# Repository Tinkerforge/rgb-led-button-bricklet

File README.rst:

RGB LED Button Bricklet
=======================

This repository contains the firmware source code and the hardware design
files. The documentation generator configs can be found at
https://github.com/Tinkerforge/generators

Repository Content
------------------

software/:
 * examples/: Examples for all supported languages
 * build/: Compiled files
 * src/: Source code of firmware
 * Makefile: Makefile to build project

hardware/:
 * Contains KiCad project files and additionally schematics as PDF

datasheets/:
 * Contains datasheets for sensors and complex ICs that are used

Hardware
--------

The hardware is designed with the open source EDA Suite KiCad
(http://www.kicad.org). Before you are able to open the files,
you have to install the Tinkerforge kicad-libraries
(https://github.com/Tinkerforge/kicad-libraries). You can either clone
them directly in hardware/ or clone them in a separate folder and
symlink them into hardware/
(ln -s kicad_path/kicad-libraries project_path/hardware). After that you
can open the .pro file in hardware/ with KiCad and from there view and
modify the schematics and the PCB layout.

Software
--------

If you want to do your own Brick/Bricklet firmware development we highly
recommend that you use our build environment setup script and read the
tutorial (https://www.tinkerforge.com/en/doc/Tutorials/Tutorial_Build_Environment/Tutorial.html).

To compile the C code we recommend you to install the newest GNU Arm Embedded
Toolchain (https://launchpad.net/gcc-arm-embedded/+download).
You also need to install bricklib2 (https://github.com/Tinkerforge/bricklib2).

You can either clone it directly in software/src/ or clone it in a
separate folder and symlink it into software/src/
(ln -s bricklib_path/bricklib2 project_path/software/src/). Finally make sure to
have CMake installed (http://www.cmake.org/cmake/resources/software.html).

After that you can build the firmware by invoking make in software/.
The firmware (.zbin) can then be found in software/build/ and uploaded
with brickv (click button "Flashing" on start screen).

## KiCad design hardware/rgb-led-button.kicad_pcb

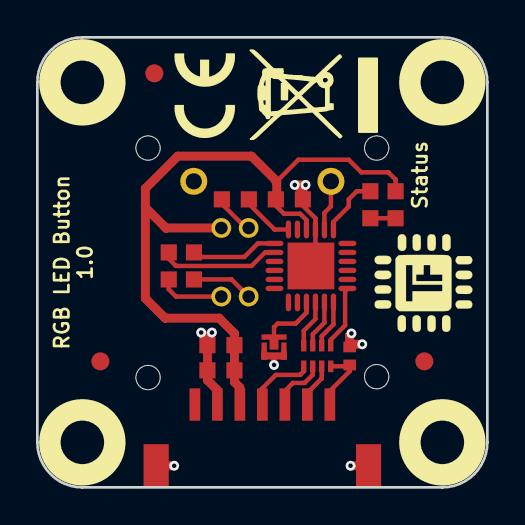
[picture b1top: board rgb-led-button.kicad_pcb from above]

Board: 2 copper layers, 25.0 x 25.0 mm, 22 parts (1 on the bottom side), 20 nets.

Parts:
C1: 220pF; C0402F
C2: 1uF; C0603F
C3: 10uF; C0603F
C4: 100nF; C0603F
D1: blue; D0603F
Fiducial_Mark: VAL**; Fiducial_Mark
Fiducial_Mark#2, Fiducial_Mark#3: VAL**; Fiducial_Mark
P1: CON-SENSOR; CON-SENSOR2
P2: Boot; SolderJumper
R1: 1k; R0603F
R2, R4: 15; R0603F
R3: 68; R0603F
RP1: 82; 4X0402
SW1: RGB_SWITCH_AD
U1: XMC1100-16; QFN24-4x4mm-0.5mm
U2, U3, U4, U5: DRILL; DRILL_NP
VAL: CE_5mm

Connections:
GND: C1.2, C2.1, C3.1, C4.1, P1.2, P1.EP, P2.1, SW1.2, U1.9, U1.EXP
unnamed: C1.1, P1.7, RP1.4
unnamed: D1.2, R1.2
unnamed: P1.4, RP1.1
unnamed: P1.5, RP1.2
unnamed: P1.6, RP1.3
unnamed: P2.2, U1.21
unnamed: R1.1, U1.7
unnamed: R2.2, SW1.B2
unnamed: R3.2, SW1.R2
unnamed: R4.2, SW1.G2
P1.0_HO: R4.1, U1.14
P1.1_HO: R3.1, U1.13
P1.2_HO: R2.1, U1.12
PinSwitch: SW1.1, U1.8
S-CLK: RP1.7, U1.23
S-CS: RP1.8, U1.22
S-MISO: RP1.5, U1.1
S-MOSI: RP1.6, U1.24
VCC: C2.2, C3.2, C4.2, D1.1, P1.3, SW1.C2, U1.10

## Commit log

2017-02-09 Add readme file
2017-02-09 initial check in
2017-02-14 Add schematic
2017-02-14 Add PCB
2017-02-14 Add fiducial marks and TF logo
2017-02-14 Add WEEE and CE logos
2017-03-01 Fix CE logo
2017-05-05 Change filtering to R/C circuit
2017-05-05 Add more 3d information (tbc)
2017-05-08 change button footprint, fix design
2017-05-08 add description
2017-05-22 add demo software for bricklet
    * primitive led dimming without pwm
2017-05-29 not finished: add led, reduce board size
2017-05-29 Fix name
2017-05-29 Add .gitignore
2017-05-29 Add Makefile and Changelog
2017-05-29 Add ccu dependency
2017-05-29 Use CCU4 to create PWM
2017-05-29 Remove define checking TODOs
2017-08-10 change bricklet to 25x25mm size
2017-08-10 fix text positions
2017-08-11 specify filter circuit
2017-08-14 fix rgb button footprint, specify resistors
2017-08-24 increase mounting holes
2017-08-24 fix button and status led pin
2017-08-24 Update gitignore file
2017-08-24 Use new ccu4_pwm function from hal
2017-08-24 Add rgb value calibration support
2017-08-24 Unify naming scheme
2017-09-08 add status led description text
2017-09-19 specify processor
2017-11-06 Add 3d information (final)
2017-11-06 Add 3d model (*.step & *.FCStd)
2017-11-06 Add final schematic
2017-11-09 Remove debugging
2017-11-16 rgb button status text fixed
2017-11-20 Rename schematic name
2017-11-20 Rename schematic properly
2017-11-20 add button datasheets
2017-11-20 Add calibration and bracket tests
2017-11-21 Remove WIP marker
2017-12-08 Add examples
2018-02-02 c: Fine-tune printf format
2018-02-19 javascript: Close div tag correctly
2018-02-20 Cleanup KiCad libraries config
    Ensure LibDir=kicad-libraries and LibName1=tinkerforge.
    Remove special library.
2018-03-05 Remove unused flash-size define
2018-05-11 Rename files
2018-05-24 perl: Use strict in examples
2018-05-28 example: Add missing dedicated print logic
2018-06-18 Change capacitor footprint(s) to C0402F
2018-06-28 Fix readme
2018-07-11 Add Makefile with docker support
2018-07-11 Update directory structure and build instructions
2018-07-11 Remove obsolete generate_makefile scripts
2018-10-04 Increase version for new release (changes in bricklib2)
2018-10-04 Add rev to changelog
2018-11-06 Add rust examples
2018-11-07 rust: Accept host names for ip connection, fix naming inconsistencies
2018-11-07 rust: Rename callback receivers.
2018-12-14 Add go examples.
2018-12-18 go: Change import path.
2018-12-18 go: Change import path again.
2018-12-20 rust: Reformat examples.
2019-01-24 mqtt: Add examples.
2019-01-24 mqtt: Fix example header.
2019-01-24 mqtt: Remove executable bit in example permissions.
2019-01-24 go: Minor example fixes.
2019-01-24 mqtt: Minor example fixes.
2019-03-28 mqtt: Fix whitespace.
2019-08-22 c: Adapt to bindings changes
2019-11-22 Remove unused period variable
2020-01-13 examples: Use python3 input instead of python2 raw_input.
2020-03-16 Whitespace
2020-04-07 examples: rust: Always block when calling bindings functions.
2020-08-19 Add uc examples.
2020-08-25 uc: Fix whitespace
2020-08-27 uc: Fix warnings.
2020-09-02 uc: Add example driver note.
2021-10-25 Update KiCad link
    https://www.kicad.org/blog/2021/10/Avoid-links-to-former-kicad-domain/
2022-04-19 examples: uc: Rename TF_HalContext to TF_HAL.
2022-04-27 uc: Adapt to bindings changes
2022-07-06 Add license files.
2025-10-04 Fix compatibility with new Docker build image (GCC 14.2.1)

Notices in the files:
hardware/rgb-led-button.kicad_pcb:
Licensed under CERN OHL v.1.1
Copyright (©) 2017, B.Nordmeyer
Copyright Tinkerforge GmbH 2017.
This documentation describes Open Hardware and is licensed under the
CERN OHL v. 1.1.
